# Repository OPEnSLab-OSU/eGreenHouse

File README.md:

# eGreenHouse

This branch is focus on the eGreenhouse HardwareX publication. If you are interested in the 3D rail, please check out the master branch and development branch.

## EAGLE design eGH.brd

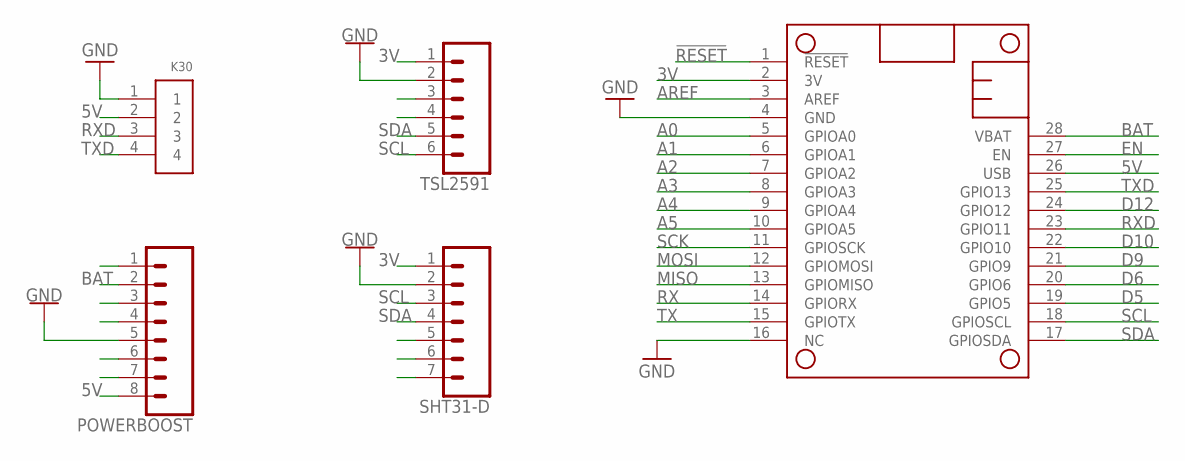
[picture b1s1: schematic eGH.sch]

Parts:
K30: 1X4-BIG; 1X04-BIG
MS1: FEATHERWING
POWERBOOST: CONN_08"; 1X08
SHT31-D: CONN_07; 1X07
TSL2591: CONN_06SILK_FEMALE_PTH; 1X06

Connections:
3V: MS1.2 (3V), SHT31-D.1, TSL2591.1
5V: K30.2, MS1.26 (USB), POWERBOOST.8
!RESET: MS1.1 (!RESET)
A0: MS1.5 (GPIOA0)
A1: MS1.6 (GPIOA1)
A2: MS1.7 (GPIOA2)
A3: MS1.8 (GPIOA3)
A4: MS1.9 (GPIOA4)
A5: MS1.10 (GPIOA5)
AREF: MS1.3 (AREF)
BAT: MS1.28 (VBAT), POWERBOOST.2
D5: MS1.19 (GPIO5)
D6: MS1.20 (GPIO6)
D9: MS1.21 (GPIO9)
D10: MS1.22 (GPIO10)
D12: MS1.24 (GPIO12)
EN: MS1.27 (EN)
GND: K30.1, MS1.4 (GND), POWERBOOST.5, SHT31-D.2, TSL2591.2
MISO: MS1.13 (GPIOMISO)
MOSI: MS1.12 (GPIOMOSI)
RX: MS1.14 (GPIORX)
RXD: K30.3, MS1.23 (GPIO11)
SCK: MS1.11 (GPIOSCK)
SCL: MS1.18 (GPIOSCL), SHT31-D.3, TSL2591.6
SDA: MS1.17 (GPIOSDA), SHT31-D.4, TSL2591.5
TX: MS1.15 (GPIOTX)
TXD: K30.4, MS1.25 (GPIO13)

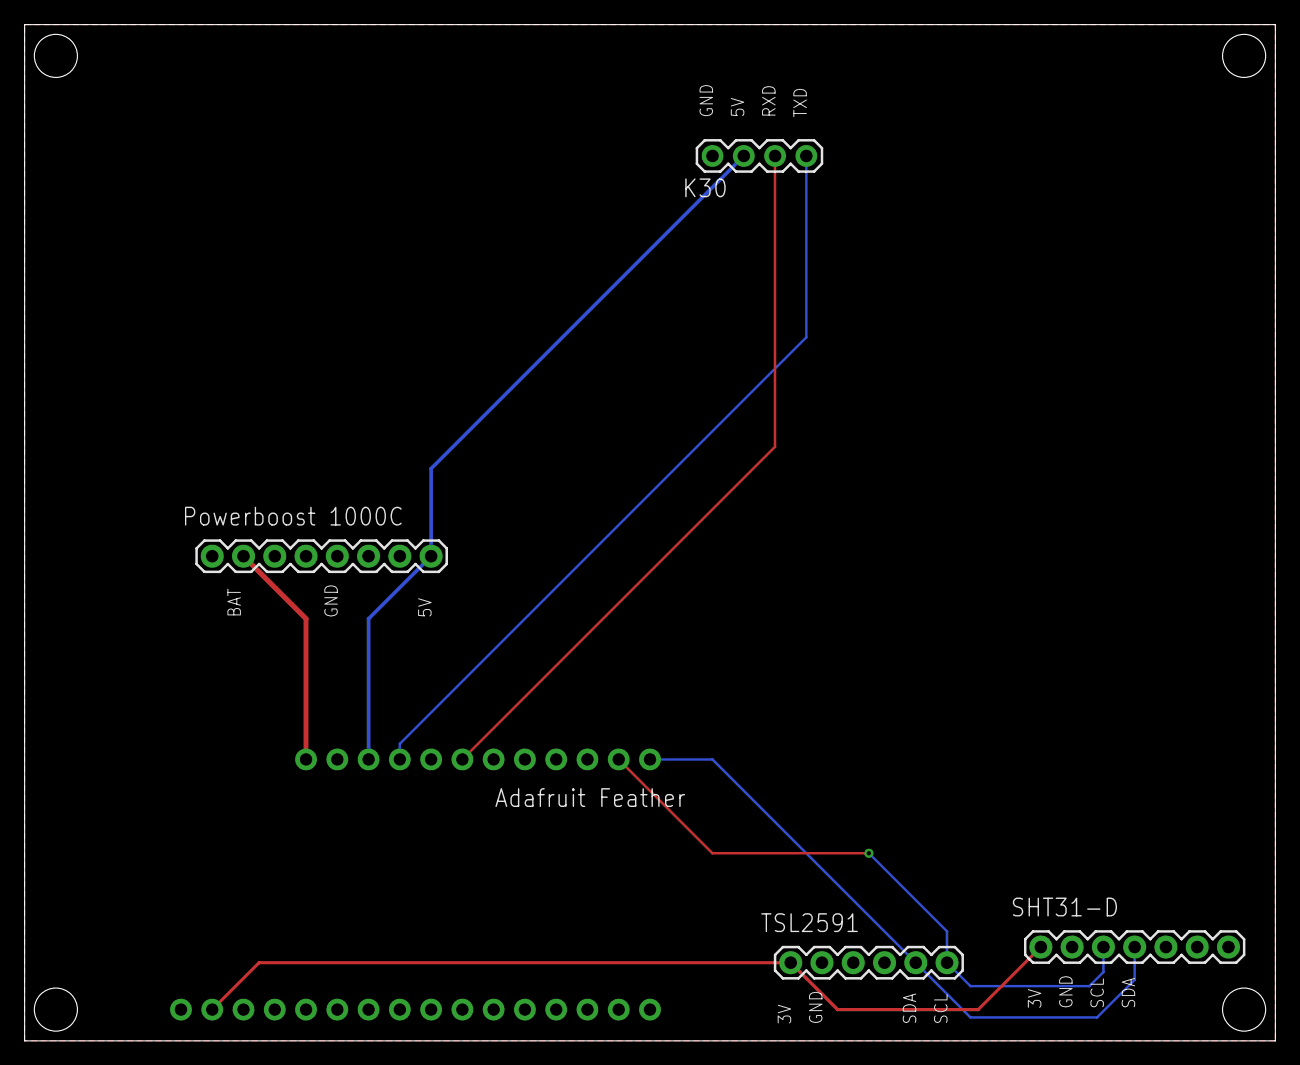
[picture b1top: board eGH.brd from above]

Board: 2 copper layers, 101.6 x 82.5 mm, 5 parts (0 on the bottom side), 8 nets.

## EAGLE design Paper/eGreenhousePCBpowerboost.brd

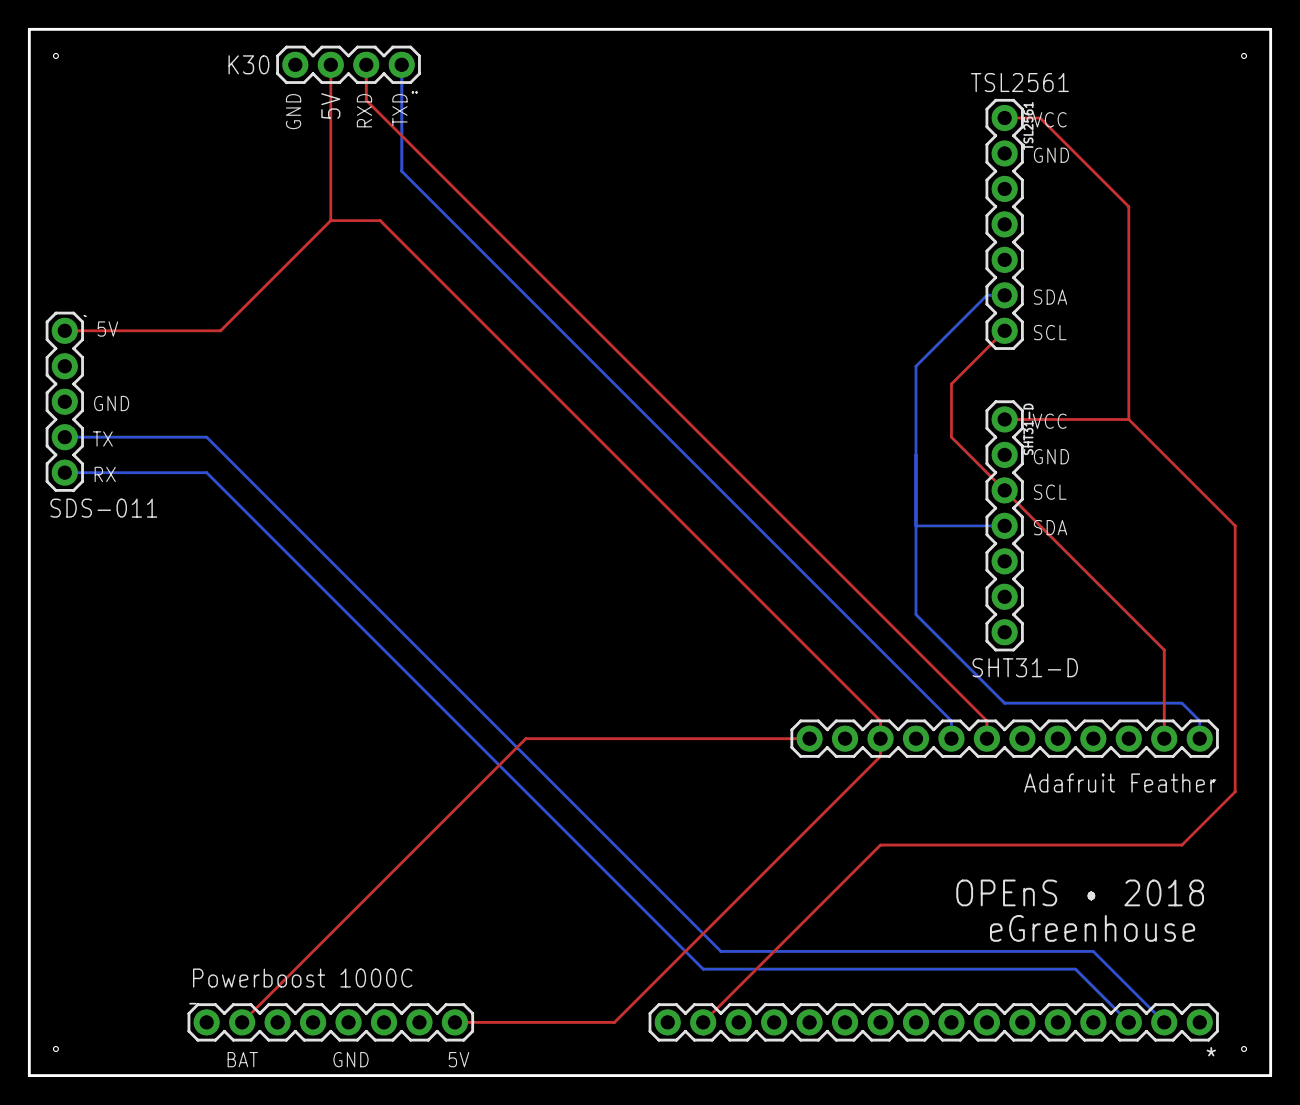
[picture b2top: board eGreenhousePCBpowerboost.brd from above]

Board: 2 copper layers, 88.9 x 74.9 mm, 7 parts (0 on the bottom side), 10 nets.

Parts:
': 1X05
*: 1X16
.: 1X12
..: 1X04
SHT31-D: 1X07
TSL2561: 1X07
_: 1X08

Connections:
5V: '.1, ..10, ...3, _.8
BAT: ..12, _.2
D11: ..7, ...2
D12: ..8, ...1
GND: '.3, *.13, ...4, SHT31-D.2, TSL2561.2, _.5
RX: '.5, *.3
SCL: ..2, SHT31-D.3, TSL2561.7
SDA: ..1, SHT31-D.4, TSL2561.6
TX: '.4, *.2
VCC: *.15, SHT31-D.1, TSL2561.1

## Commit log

2018-06-07 Create Documentation
2019-05-28 Specifying a more detailed and up to date setup.
2019-05-28 Adding dependencies section.
2019-05-28 Sensor module assembly pictures
2019-05-31 Organizing code and fixing radio error
2019-05-31 Updating dependencies list.
2019-05-31 Adding issues and updates section
2019-06-03 Fixing bug that makes ethernet hub stall if setup doesn't work on the second try.
2020-04-15 Sensor Package is Complete
2020-05-05 Future plans are lay outed, not tested nor completed yet
2020-05-06 Revert "Future plans are lay outed, not tested nor completed yet"
    This reverts commit 4542ce00d311c982bfb5c88f17e681c7a869f9fd.
2020-05-26 Did a reasonable intergration between the HyperRail and HyperDrive code with the Hub, Need to test it
2020-05-26 added the Json to String and String to Json for package delivery
2020-06-17 Only communication between Sensor Package to Ethernet/Wifi
2020-06-17 Hide my personal information
2020-06-19 Worked on the code to make it work
2020-06-19 Code works fine fully
2020-06-22 Add the paper documentation
2020-06-23 Made just for K30 Communication
2020-06-25 Working on the paper
2020-06-26 Sensor Package and Hub Communcation with Raw LoRa is working
2020-06-30 Send Data to the HyperRail for the Coordinates
2020-07-01 Almost working, just need to test the update on GoogleSheets
2020-07-01 Just need to test internet and issue with GUI
2020-07-02 Internet test not done, Update GUI, LoRa Issue kinda solved
2020-07-02 Com port
2020-07-07 Working on the LoRa
2020-07-08 Revert "Working on the LoRa"
    This reverts commit adb73dfa4af887359dd4bd9c7c0ba208c687a937.
2020-07-08 Revert "Internet test not done, Update GUI, LoRa Issue kinda solved"
    This reverts commit db6bc57ac0cda35ed4e0b0cd30fd3f7ac2f430d0.
2020-07-08 Most stable version so far
2020-07-08 Working on LoRa Communication
2020-07-09 GUI updated, LoRa Issue still
2020-07-11 Almost done, just need to test
2020-07-11 Made some changes, just need to test:
2020-07-11 Log Arduino to GUI
2020-07-11 Add timer for the GUI and Console Log
2020-07-12 Done! Everything works!
2020-07-13 Add README.MD
2020-07-13 Now Complete
2020-07-13 Except the Hyper Movement code, we are done
2020-07-15 Added Movement code, complete!
2020-07-15 Testing
2020-07-20 Updating to 1D rail
2020-07-21 Trying with Spool
2020-07-22 Build up step complete
2020-07-22 Modify the code to 1D rail
2020-07-23 The paper is almost done
2020-07-28 Spool Config
2020-07-28 Still need work on the config part
2020-07-30 Spool Trying
2020-07-31 eGreenhouse HardwareX Paper from 3 to 6 is complete, I think and hope...
2020-08-11 Spool is now able to work properly
2020-09-01 Design files for the paper
2020-09-02 Update json for Zenodo
2020-09-02 Change .Zenodo.json
2020-09-02 Update License
2020-09-02 Update zenodo
2020-09-18 Updated code due to update with Loom
2020-09-18 Modify the code as long with Loom updates
2020-09-18 Able with Hypnos and updated the code as long with Loom
2020-09-18 Remove a comment
2020-09-22 Updated the code: Works better with PCB
2020-09-23 Update comments and fix some bugs
2020-09-23 Might add non-Hypnos version for eGH
2020-09-23 Added non-hypnos version for eGH_Sensor_Package
2020-09-23 Update Radio and K30 pin
2020-10-09 Solved #7 and #10
2020-10-10 Update layout and now able to publish
2020-10-10 Now with 3 boards rather than 4
2020-10-21 Add GoogleSheet Script
2020-10-21 Add GoogleSheet.gs file and updated Hub code
2020-10-21 Create README.md
    Letting people know that this branch is for eGreenhouse publication
2020-11-02 Change some parts to make it better
2020-11-05 Update non-hypnos version

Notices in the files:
parts and their libraries:
SparkFun-Connectors: Licensing: Creative Commons ShareAlike 4.0 International - https://creativecommons.org/licenses/by-sa/4.0
